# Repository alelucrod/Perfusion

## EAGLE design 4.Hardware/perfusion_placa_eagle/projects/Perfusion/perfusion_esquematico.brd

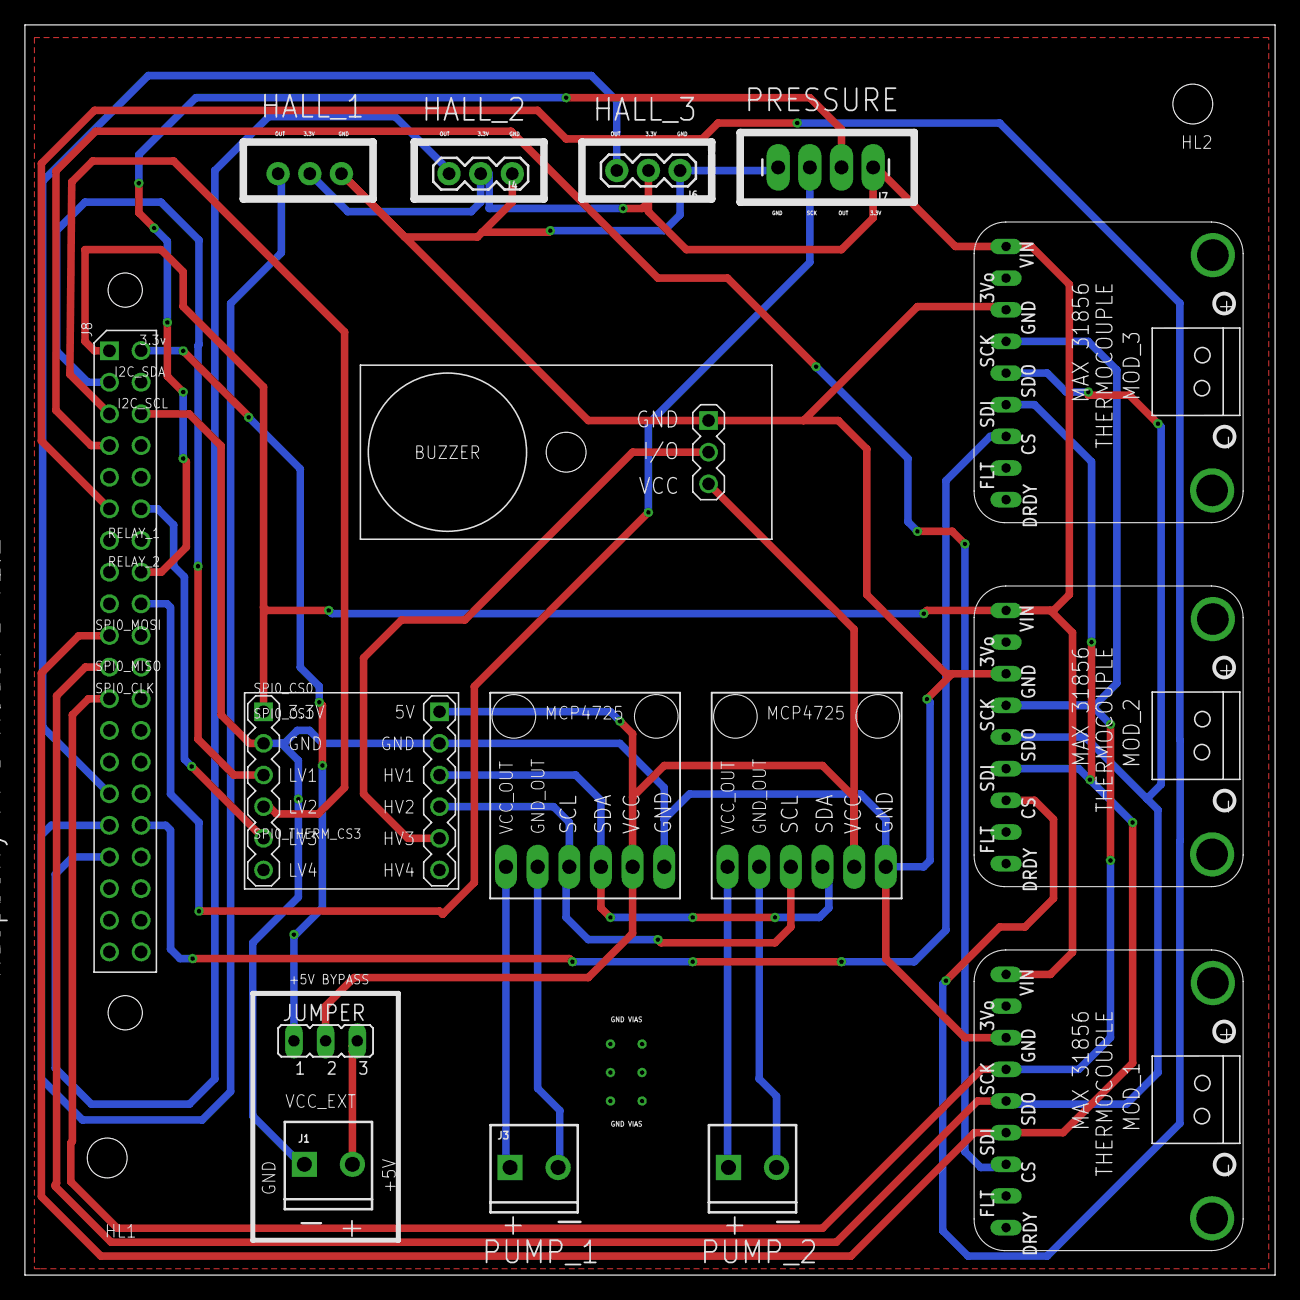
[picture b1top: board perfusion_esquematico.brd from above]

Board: 2 copper layers, 100.3 x 100.3 mm, 16 parts (1 on the bottom side), 26 nets.

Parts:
J1, J2, J3: SCREWTERMINAL-3.5MM-2_LOCK
J4, J5, J6: 1X03
J7: 1X04_LONGPADS
JUMPER: JP2
PCB1: RPI3
U$2: SOUND-BUZZER
U$3: LEVEL-SHIFTER-4CH
U$4, U$5, U$6: MAX31856
U$7, U$8: LIB1MCP4725_ABF; LIB1

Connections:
BUZZER_IN: PCB1.P$12, U$3.J1.5
BUZZER_OUT_5V: U$2.2, U$3.J2.5
DOUT_BAR: J7.2, PCB1.P$16
HALL1: J4.3, PCB1.P$33
HALL2: J5.3, PCB1.P$31
HALL3: J6.3, PCB1.P$29
I2C_SCL: PCB1.P$5, U$3.J1.4
I2C_SCL_5V: U$3.J2.4, U$7.SCL, U$8.SCL
I2C_SDA: PCB1.P$3, U$3.J1.3
I2C_SDA_5V: U$3.J2.3, U$7.SDA, U$8.SDA
MCP_1_GND: J2.2, U$8.GND2
MCP_1_VSS: J2.1, U$8.OUT
MCP_2_GND: J3.2, U$7.GND2
MCP_2_VSS: J3.1, U$7.OUT
RPI3_+3V: J4.2, J5.2, J6.2, J7.1, PCB1.P$1, U$3.J1.1, U$4.PINES1, U$5.PINES1, U$6.PINES1
RPI3_+5V: JUMPER.2, U$2.3, U$3.J2.1, U$7.VCC, U$8.VCC
RPI3_+5V_IN: JUMPER.1, PCB1.P$2
RPI3_GND: J1.1, J4.1, J5.1, J6.1, J7.4, PCB1.P$6, U$2.1, U$3.J1.2, U$3.J2.2, U$4.PINES3, U$5.PINES3, U$6.PINES3, U$7.GND, U$8.GND
SCK_BAR: J7.3, PCB1.P$18
SPI0_CLK: PCB1.P$23, U$4.PINES4, U$5.PINES4, U$6.PINES4
SPI0_CS0: PCB1.P$11, U$4.PINES7
SPI0_CS1: PCB1.P$7, U$5.PINES7
SPI0_MISO: PCB1.P$21, U$4.PINES5, U$5.PINES5, U$6.PINES5
SPI0_MOSI: PCB1.P$19, U$4.PINES6, U$5.PINES6, U$6.PINES6
SUPPLY_+5V: J1.2, JUMPER.3
THERMO_CS3: PCB1.P$32, U$6.PINES7

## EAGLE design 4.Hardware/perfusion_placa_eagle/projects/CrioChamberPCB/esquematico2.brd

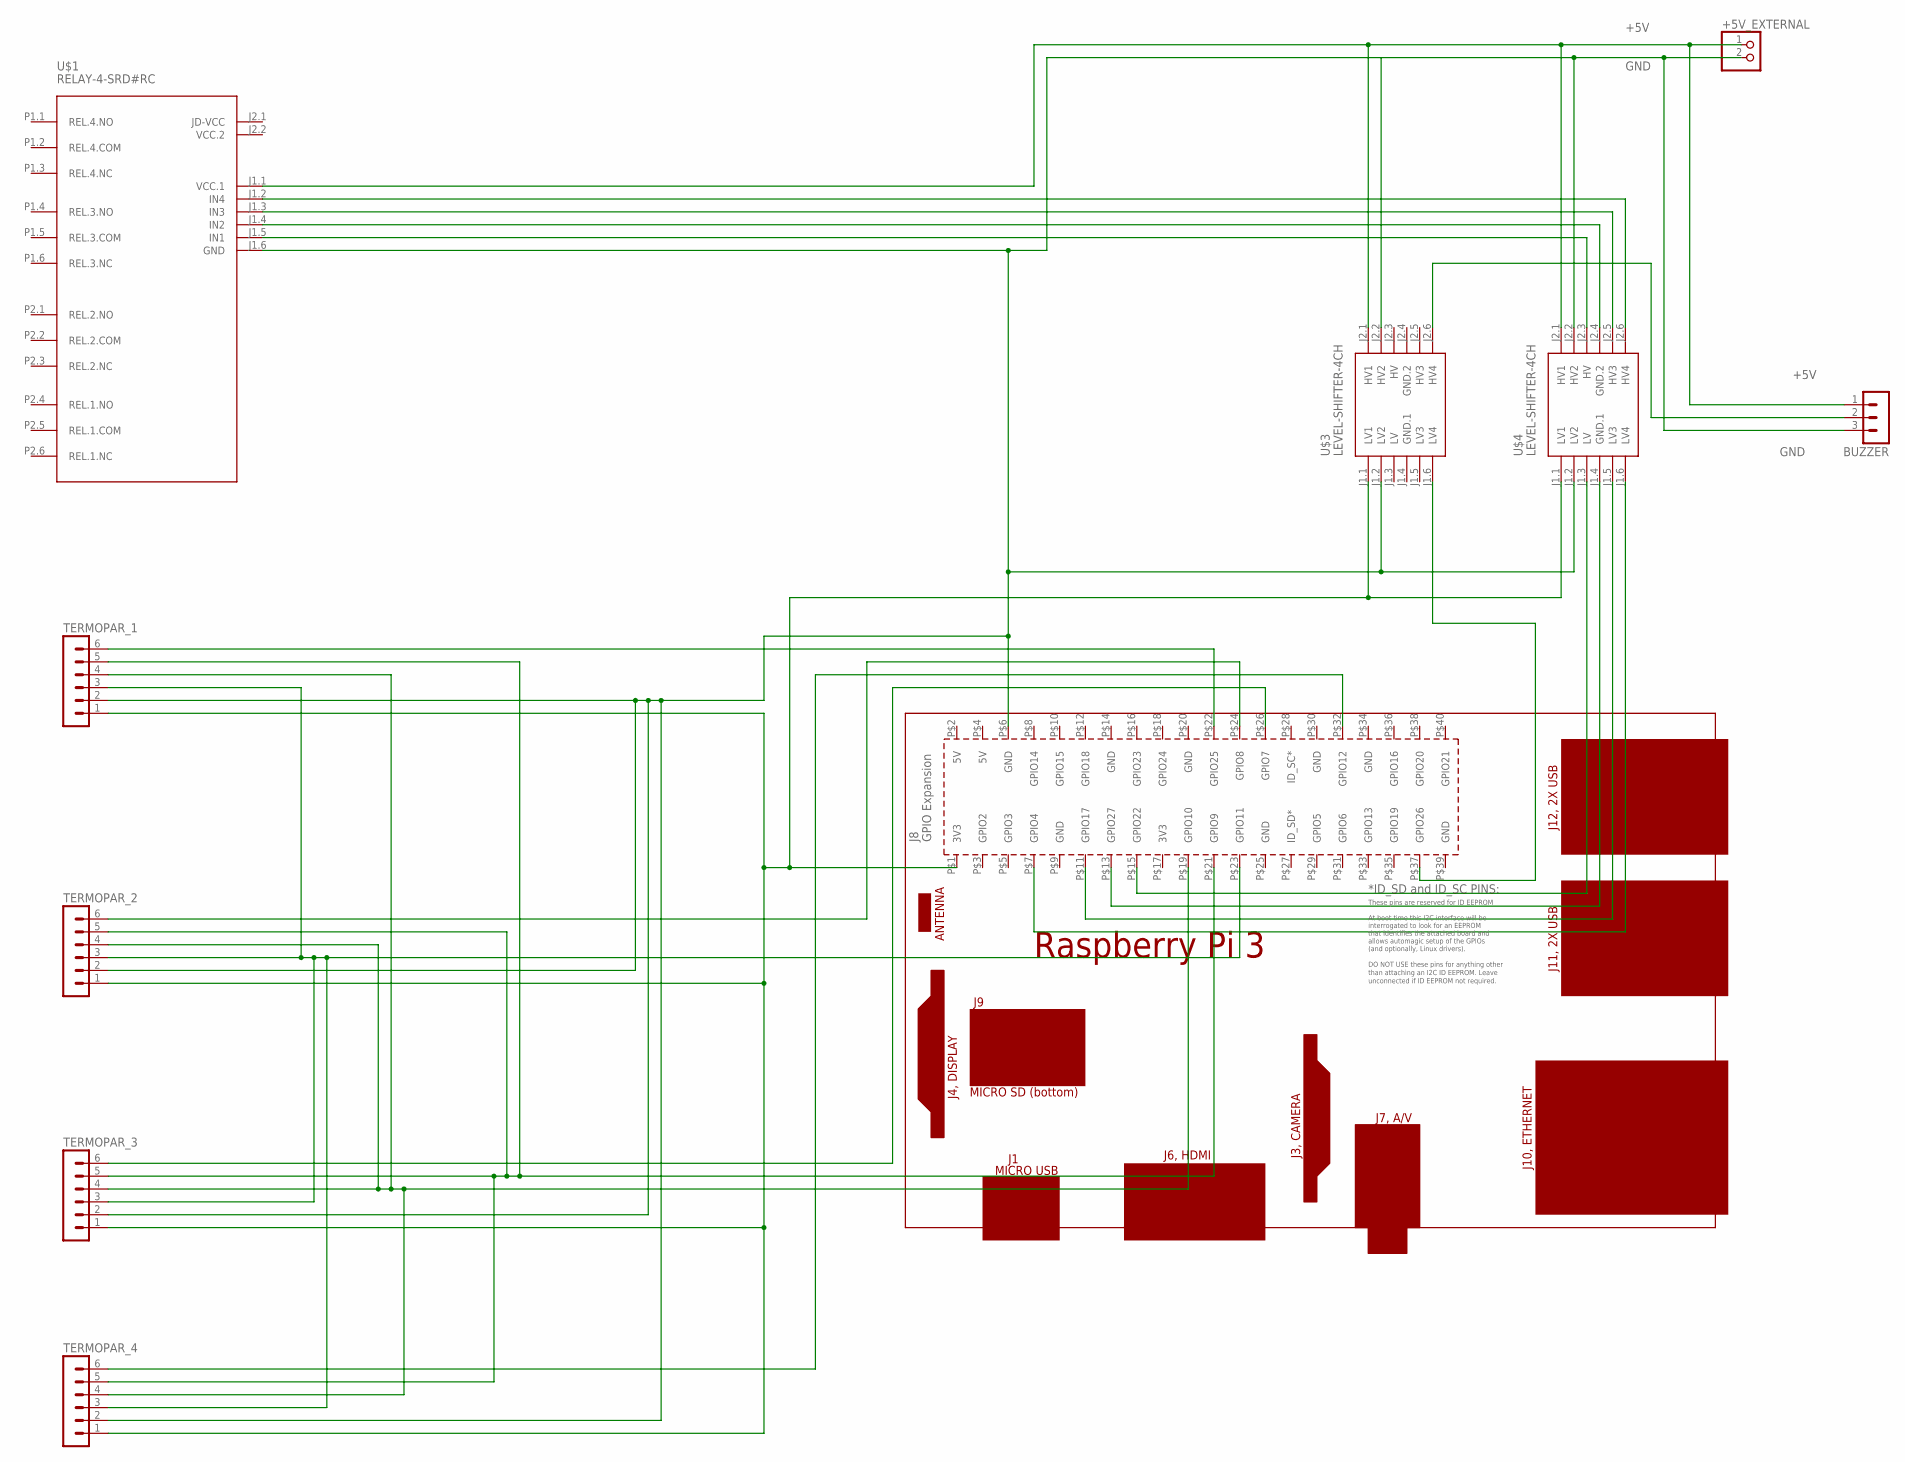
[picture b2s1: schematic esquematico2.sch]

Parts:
+5V_EXTERNAL: PINHD-1X2; 1X02
BUZZER: MA03-1
PCB1: RPI3RPI3; RPI3
TERMOPAR_1, TERMOPAR_2, TERMOPAR_3, TERMOPAR_4: MA06-1
U$1: RELAY-4-SRD#RC
U$3, U$4: LEVEL-SHIFTER-4CH

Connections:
+5V: +5V_EXTERNAL.1, BUZZER.1, U$1.J1.1 (VCC.1), U$3.J2.1 (HV1), U$4.J2.1 (HV1)
GND: +5V_EXTERNAL.2, BUZZER.3, PCB1.P$6 (GND), TERMOPAR_1.2, TERMOPAR_2.2, TERMOPAR_3.2, TERMOPAR_4.2, U$1.J1.6 (GND), U$3.J1.2 (LV2), U$3.J2.2 (HV2), U$4.J1.2 (LV2), U$4.J2.2 (HV2)
GND.1: U$3.J1.4 (GND.1)
GND.2: U$3.J2.4 (GND.2)
HV: U$3.J2.3 (HV)
LV: U$3.J1.3 (LV)
unnamed: U$1.J1.2 (IN4), U$4.J2.6 (HV4)
unnamed: U$1.J1.3 (IN3), U$4.J2.5 (HV3)
unnamed: U$1.J1.4 (IN2), U$4.J2.4 (GND.2)
unnamed: U$1.J1.5 (IN1), U$4.J2.3 (HV)
unnamed: PCB1.P$15 (GPIO22), U$4.J1.3 (LV)
unnamed: PCB1.P$13 (GPIO27), U$4.J1.4 (GND.1)
unnamed: PCB1.P$11 (GPIO17), U$4.J1.5 (LV3)
unnamed: PCB1.P$7 (GPIO4), U$4.J1.6 (LV4)
unnamed: PCB1.P$37 (GPIO26), U$3.J1.6 (LV4)
unnamed: BUZZER.2, U$3.J2.6 (HV4)
unnamed: PCB1.P$1 (3V3), TERMOPAR_1.1, TERMOPAR_2.1, TERMOPAR_3.1, TERMOPAR_4.1, U$3.J1.1 (LV1), U$4.J1.1 (LV1)
unnamed: PCB1.P$23 (GPIO11), TERMOPAR_1.3, TERMOPAR_2.3, TERMOPAR_3.3, TERMOPAR_4.3
unnamed: PCB1.P$19 (GPIO10), TERMOPAR_1.4, TERMOPAR_2.4, TERMOPAR_3.4, TERMOPAR_4.4
unnamed: PCB1.P$21 (GPIO9), TERMOPAR_1.5, TERMOPAR_2.5, TERMOPAR_3.5, TERMOPAR_4.5
unnamed: PCB1.P$22 (GPIO25), TERMOPAR_1.6
unnamed: PCB1.P$24 (GPIO8), TERMOPAR_2.6
unnamed: PCB1.P$26 (GPIO7), TERMOPAR_3.6
unnamed: PCB1.P$32 (GPIO12), TERMOPAR_4.6
VCC.2: U$1.J2.2 (VCC.2)

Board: 2 copper layers, 10 parts (0 on the bottom side), 20 nets, no tracks yet.

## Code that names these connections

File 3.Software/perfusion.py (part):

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
pin_buzzer = 18

pin_i2c_sda = 7
pin_i2c_scl = 8

pin_spi0_mosi = 9
pin_spi0_miso = 10
pin_spi0_sclk = 11
pin_spi0_cs0  = 12
pin_spi0_cs1  = 13
pin_spi0_cs2  = 14

i2c_pump1_addr = '0x00'
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        pin_relay1 = int(self.lineEdit_relay1.text())
        pin_relay2 = int(self.lineEdit_relay2.text())
        pin_buzzer = int(self.lineEdit_buzzer.text())
        pin_i2c_sda = int(self.lineEdit_i2c_sda.text())
        pin_i2c_scl = int(self.lineEdit_i2c_scl.text())
        pin_spi0_mosi = int(self.lineEdit_spi0_mosi.text())
        pin_spi0_miso = int(self.lineEdit_spi0_miso.text())
        pin_spi0_sclk = int(self.lineEdit_spi0_sclk.text())
        pin_spi0_cs0 = int(self.lineEdit_spi0_cs0.text())
        pin_spi0_cs1 = int(self.lineEdit_spi0_cs1.text())
        pin_spi0_cs2 = int(self.lineEdit_spi0_cs2.text())
        i2c_pump1_addr = str(self.comboBox_i2c_pump1.currentText())
        i2c_pump2_addr = str(self.comboBox_i2c_pump2.currentText())
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        self.lineEdit_relay2.setText(str(pin_relay2))
        self.lineEdit_buzzer.setText(str(pin_buzzer))

        self.lineEdit_i2c_sda.setText(str(pin_i2c_sda))
        self.lineEdit_i2c_scl.setText(str(pin_i2c_scl))

        self.lineEdit_spi0_mosi.setText(str(pin_spi0_mosi))
        self.lineEdit_spi0_miso.setText(str(pin_spi0_miso))
        self.lineEdit_spi0_sclk.setText(str(pin_spi0_sclk))
        self.lineEdit_spi0_cs0.setText(str(pin_spi0_cs0))
        self.lineEdit_spi0_cs1.setText(str(pin_spi0_cs1))
        self.lineEdit_spi0_cs2.setText(str(pin_spi0_cs2))


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
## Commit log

2020-02-18 [ADD] Creada estructura de directorios
2020-02-22 [MOD] Agregado los ficheros del proyecto
2020-02-22 [ADD] Añadida borrador de interfaz
2020-02-22 [MOD] Añadido nuevos comentarios
2020-02-26 [MOD] Agregada nuevas opciones de seleccion
2020-02-26 [MOD] Cambiados identificadores
2020-02-26 [MOD] Todos nombres identificadores
2020-02-27 [MOD]Rectificación unidades [MOD] Añadidos botones protocols
2020-02-27 [MOD] Añadidos botones pestaña protocols
2020-02-29 [MOD] Reestructuracion + opciones de agregar filas a tabla
2020-02-29 [MOD] Agregada columna duration
2020-03-08 [MOD] interfaz acabada antes de cambios de Ramón
2020-03-16 [MOD] Nueva interfaz
2020-03-17 [MOD] Actualizada la interfaz
2020-03-17 [MOD] Actualizado los nombres de la gui
2020-03-17 [ADD] Test efecto hall
2020-03-18 [ADD] Logos y Modelo 3D soporte
2020-03-19 [MOD] Sólo modo caudal
2020-03-24 [MOD] Diseño Hardware
2020-03-24 [MOD] Fixes hardware
2020-03-28 [MOD] Interfaz a espera de Ale

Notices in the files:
parts and their libraries:
diy-modules: Released under the Creative Commons Attribution 4.0 International License: http://creativecommons.org/licenses/by/4.0
SparkFun-Connectors: Licensing: Creative Commons ShareAlike 4.0 International - https://creativecommons.org/licenses/by-sa/4.0
